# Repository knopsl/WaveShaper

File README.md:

# VC 4046 Wave Shaper

**Prototype has been tested, some issues found. Corrected version not yet tested! ASSUME NOTHING WORKS UNTIL THIS NOTICE IS REMOVED!**

This is a modification of the Barton Musical Circuits [4046 Wave Shaper](http://www.bartonmusicalcircuits.com/4046/), a module described by Barton as follows:

> This is an all analog synthesizer module used to create new timbres and waveforms with your existing VCOs. It uses a CD4046 phase locked loop chip in combination with a binary counter to multiply the frequency of the input signal. It then has 7 outputs divided down from that multiplied frequency which are mixed together. It's simple to use and has a distinct sound.

In Barton's design the seven signals (which are 0, 1, 2, and 3 octaves above and below the input signal) go into a simple mixer with a potentiometer attenuator on each channel to produce the module output. This modification replaces that simple mixer with a voltage controlled mixer, allowing use of control voltages to modulate the mix. If any of the seven control voltage jacks does not have anything plugged in, the CV is normalled to +10 V allowing the pot to behave like a signal attenuator.

An additional modification to Barton's design is that the gain on the output stage can be varied using a pot on the panel. This allows reducing the gain to avoid clipping when mixing multiple large signals, avoiding the need to turn down all the channel pots and allowing use of their full range.

The module consists of a front panel and three PCBs. One of these is the PCB for the original 4046 Wave Shaper, available from Barton, assembled mostly as designed but with a few things changed. The second is a PCB holding the board mounted pots and switch as well as the parts associated with the voltage controlled mixer and the power input section. The third just holds the board mounted input and output jacks.

## Photos

to be added

## Documentation

* [Schematic](Docs/waveshaper.pdf)
* PCB layout: [front](Docs/waveshaper_layout_front.pdf), [back](Docs/waveshaper_layout_back.pdf)
* [BOM](Docs/waveshaper_bom.md)
* [Build notes](Docs/build.md)

## GitHub repository

* [https://github.com/holmesrichards/WaveShaper](https://github.com/holmesrichards/WaveShaper)

## Submodules

This repo uses submodules aoKicad and Kosmo_panel, needed by KiCad. To clone:

```
git clone git@github.com:holmesrichards/WaveShaper.git
git submodule init
git submodule update
```

Alternatively do

```
git clone --recurse-submodules git@github.com:holmesrichards/WaveShaper.git
```

Or if you download the repository as a zip file, you must also click on the "aoKicad" and "Kosmo\_panel" links on the GitHub page (they'll have "@ something" after them) and download them as separate zip files which you can unzip into this repo's aoKicad and Kosmo\_panel directories.

If desired, copy the files from aoKicad and Kosmo\_panel to wherever you prefer (your KiCad user library directory, for instance, if you have one). Then in KiCad, add symbol libraries 

```
aoKicad/ao_symbols
Kosmo_panel/Kosmo
```
and footprint libraries 
```
aoKicad/ao_tht
Kosmo_panel/Kosmo_panel.
```

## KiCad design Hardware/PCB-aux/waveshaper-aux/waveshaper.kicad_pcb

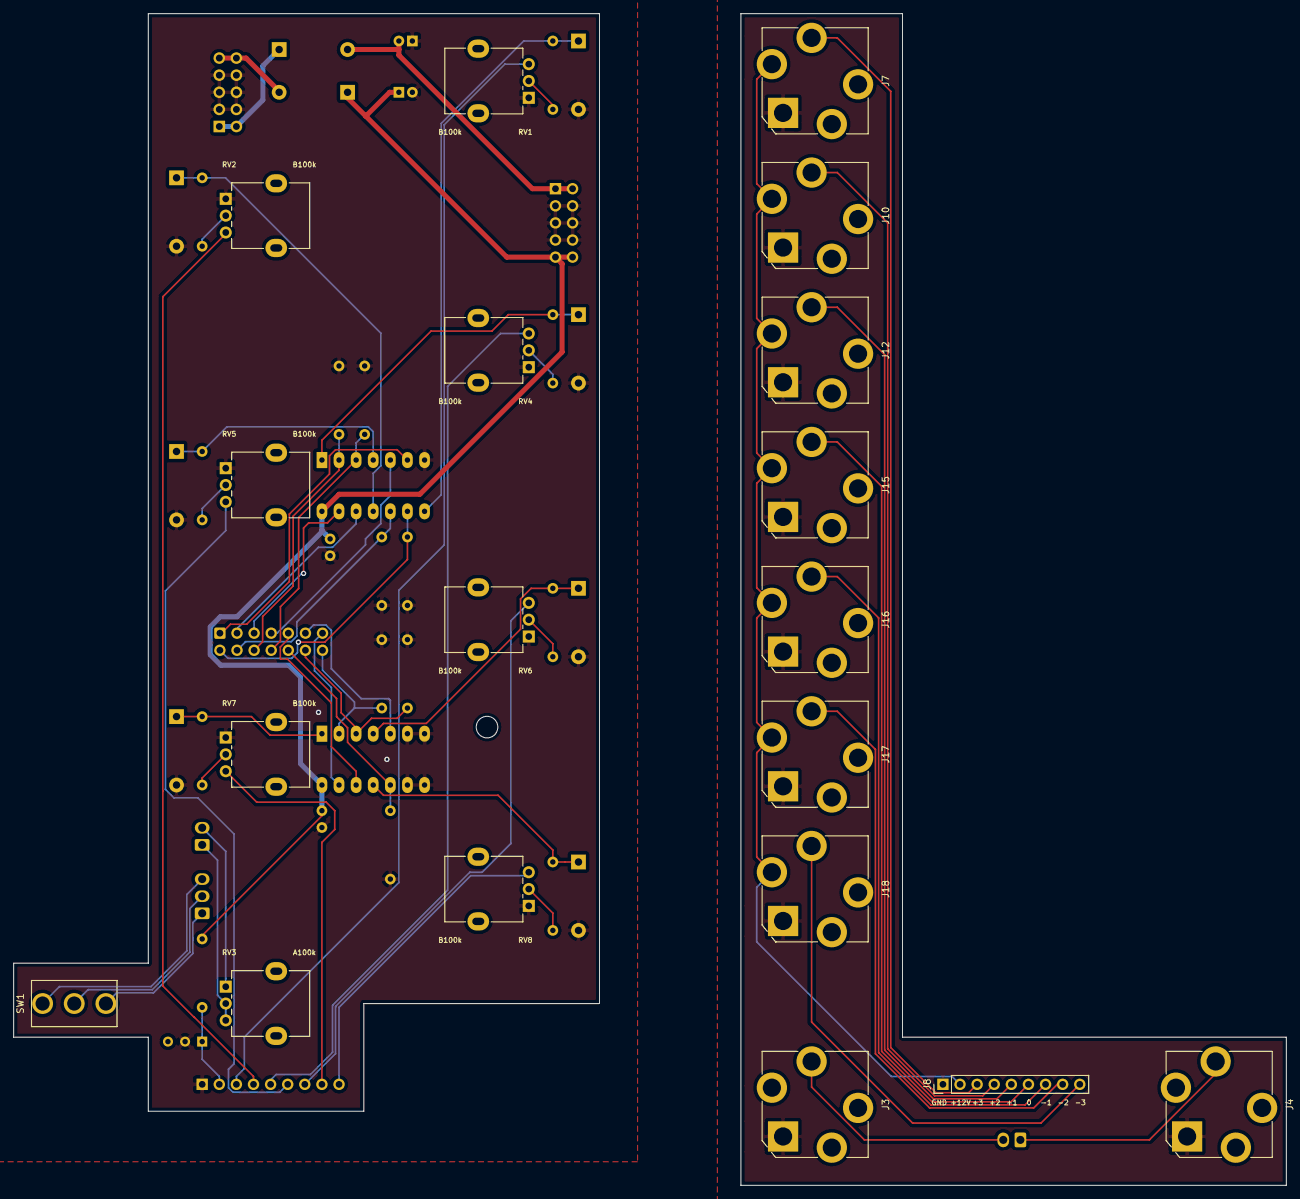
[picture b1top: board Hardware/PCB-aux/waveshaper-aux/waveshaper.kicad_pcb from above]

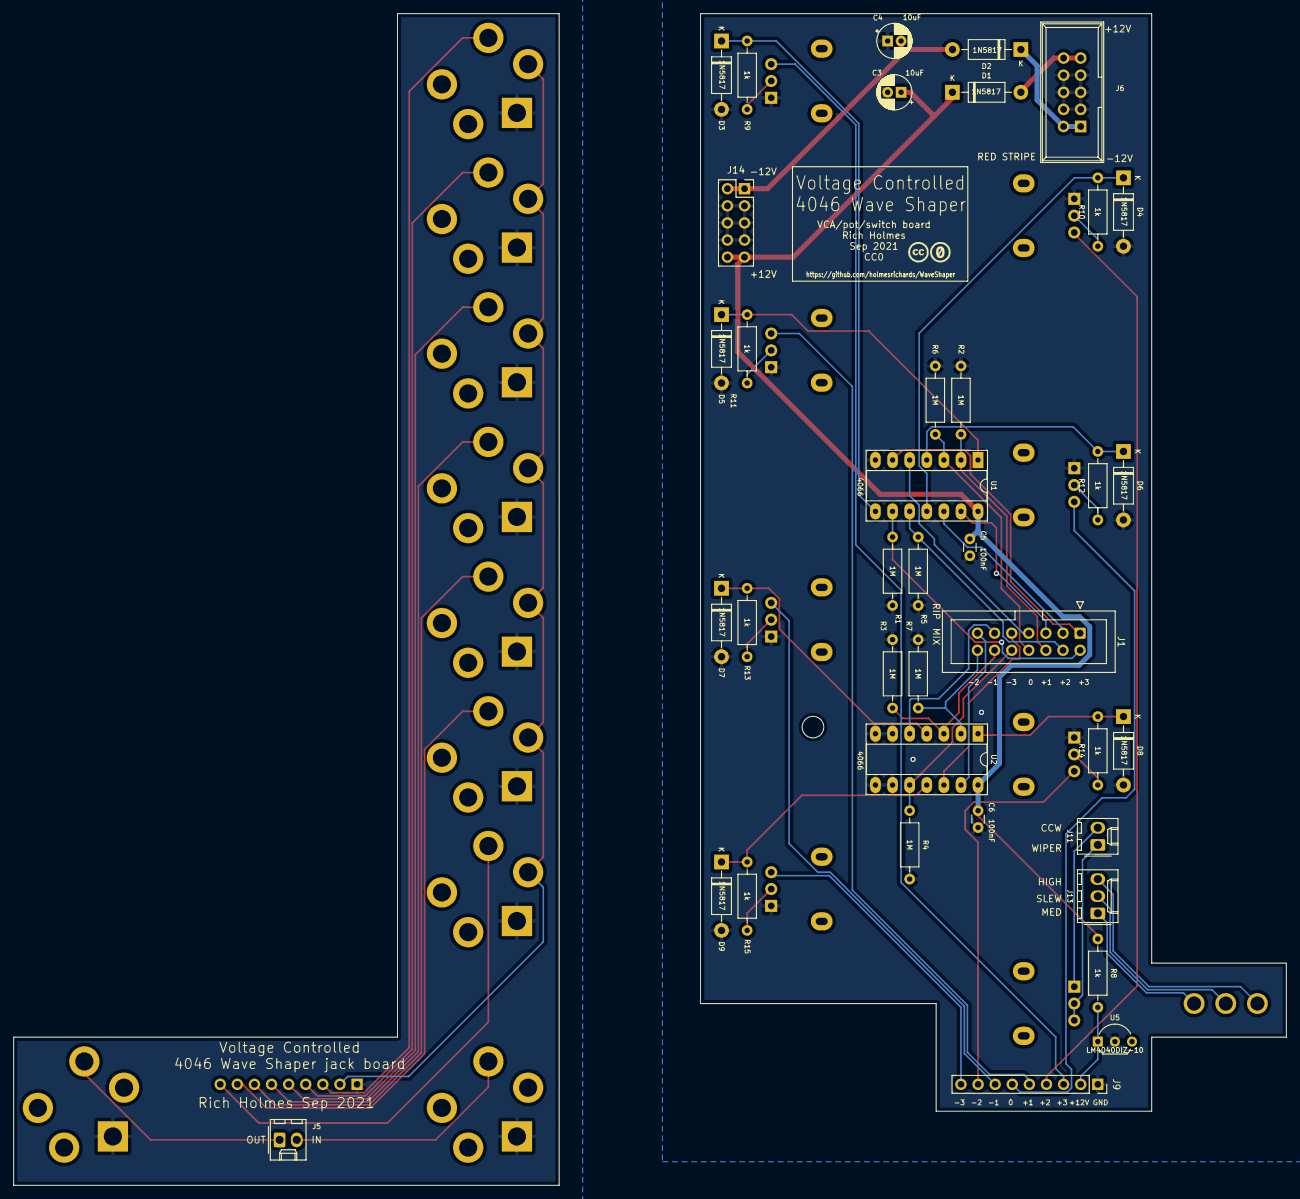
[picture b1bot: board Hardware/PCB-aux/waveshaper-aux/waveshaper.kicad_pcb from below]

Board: 2 copper layers, 87.0 x 163.0 mm, 60 parts (39 on the bottom side), 57 nets.

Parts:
C3, C4: 10uF; CP_Radial_D5.0mm_P2.00mm
C5, C6: 100nF; C_Disc_D3.0mm_W1.6mm_P2.50mm
D1, D2, D3, D4, D5, D6, D7, D8, D9: 1N5817; D_DO-41_SOD81_P10.16mm_Horizontal
GRAF1: CC0 logo; CC0_logo
GRAF2: Holes; waveshaper-holes
H1: MountingHole; MountingHole_3.2mm_M3
J1: 2x7 IDC header; IDC-Header_2x07_P2.54mm_Vertical
J3, J4: AudioJack2; Jack_6.35mm_PJ_629HAN
J5, J11: 2_pin_Molex_header; Molex_KK-254_AE-6410-02A_1x02_P2.54mm_Vertical
J6: EURO_PWR_2x5; Power_Header
J7, J10, J12, J15, J16, J17, J18: AudioJack2_SwitchT; Jack_6.35mm_PJ_629HAN
J8: Conn_01x9; PinHeader_1x09_P2.54mm_Vertical
J9: Conn_01x9; PinSocket_1x09_P2.54mm_Vertical
J13: 3_pin_Molex_header; Molex_KK-254_AE-6410-03A_1x03_P2.54mm_Vertical
J14: 2x5 pin socket; PinSocket_2x05_P2.54mm_Vertical
R1, R2, R3, R4, R5, R6, R7: 1M; R_Axial_DIN0207_L6.3mm_D2.5mm_P10.16mm_Horizontal
R8, R9, R10, R11, R12, R13, R14, R15: 1k; R_Axial_DIN0207_L6.3mm_D2.5mm_P10.16mm_Horizontal
RV1, RV2, RV4, RV5, RV6, RV7, RV8: B100k; Potentiometer_Alpha_RD901F-40-00D_Single_Vertical
RV3: A100k; Potentiometer_Alpha_RD901F-40-00D_Single_Vertical
SW1: SW_SPDT; SPDT-toggle-switch-1M-series
U1, U2: 4066; DIP-14_W7.62mm_Socket_LongPads
U5: LM4040DIZ-10; TO-92_Inline_Wide

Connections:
+10V: J9.2, R8.2, U5.1
+12V: C3.1, C5.1, C6.1, D1.1, J14.9, J14.10, R8.1, U1.14, U2.14
-12V: C4.2, D2.2, J14.1, J14.2
/Panel and power/+12V_IN: D1.2, J6.9, J6.10
/Panel and power/-12V_IN: D2.1, J6.1, J6.2
/Panel and power/CVIN_0: J8.6, J15.T
/Panel and power/CVIN_+1: J8.5, J12.T
/Panel and power/CVIN_+2: J8.4, J10.T
/Panel and power/CVIN_+3: J7.T, J8.3
/Panel and power/CVIN_-1: J8.7, J16.T
/Panel and power/CVIN_-2: J8.8, J17.T
/Panel and power/CVIN_-3: J8.9, J18.T
/Panel and power/IN: J3.T, J5.2
/Panel and power/LEVEL_CCW: J11.2, RV3.1
/Panel and power/LEVEL_WIPER: J11.1, RV3.2, RV3.3
/Panel and power/OUT: J4.T, J5.1
/Panel and power/SLEW: J13.2, SW1.2
/Panel and power/SL_HIGH: J13.3, SW1.3
/Panel and power/SL_MED: J13.1, SW1.1
/RIPOUT_0: J1.7, U1.5
/RIPOUT_+1: J1.5, U1.13
/RIPOUT_+2: J1.3, U1.12
/RIPOUT_+3: J1.1, U1.6
/RIPOUT_-1: J1.11, U2.5
/RIPOUT_-2: J1.13, U2.13
/RIPOUT_-3: J1.9, U2.12
CV_0: D6.1, R12.2, U1.4
CV_+1: D5.1, R11.2, U1.1
CV_+2: D4.1, R10.2, U1.11
CV_+3: D3.1, R9.2, U1.8
CV_-1: D7.1, R13.2, U2.4
CV_-2: D8.1, R14.2, U2.1
CV_-3: D9.1, R15.2, U2.11
GND: C3.2, C4.1, C5.2, C6.2, D3.2, D4.2, D5.2, D6.2, D7.2, D8.2, D9.2, J6.3, J6.4, J6.5, J6.6, J6.7, J6.8, J9.1, J14.3, J14.4, J14.5, J14.6, J14.7, J14.8, R1.2, R2.2, R3.2, R4.2, R5.2, R6.2, R7.2, RV1.1, RV2.1, RV4.1, RV5.1, RV6.1, RV7.1, RV8.1, U1.7, U2.6, U2.7, U2.8, U2.9, U5.2
GND1: J3.S, J4.S, J7.S, J8.1, J10.S, J12.S, J15.S, J16.S, J17.S, J18.S
J10V: J7.TN, J8.2, J10.TN, J12.TN, J15.TN, J16.TN, J17.TN, J18.TN
MIXIN_0: J1.8, R6.1, U1.3
MIXIN_+1: J1.6, R2.1, U1.2
MIXIN_+2: J1.4, R5.1, U1.10
MIXIN_+3: J1.2, R1.1, U1.9
MIXIN_-1: J1.12, R3.1, U2.3
MIXIN_-2: J1.14, R7.1, U2.2
MIXIN_-3: J1.10, R4.1, U2.10
unnamed: J9.3, RV1.3
unnamed: J9.4, RV2.3
unnamed: J9.5, RV4.3
unnamed: J9.6, RV5.3
unnamed: J9.7, RV6.3
unnamed: J9.8, RV7.3
unnamed: J9.9, RV8.3
unnamed: R9.1, RV1.2
unnamed: R10.1, RV2.2
unnamed: R11.1, RV4.2
unnamed: R12.1, RV5.2
unnamed: R13.1, RV6.2
unnamed: R14.1, RV7.2
unnamed: R15.1, RV8.2

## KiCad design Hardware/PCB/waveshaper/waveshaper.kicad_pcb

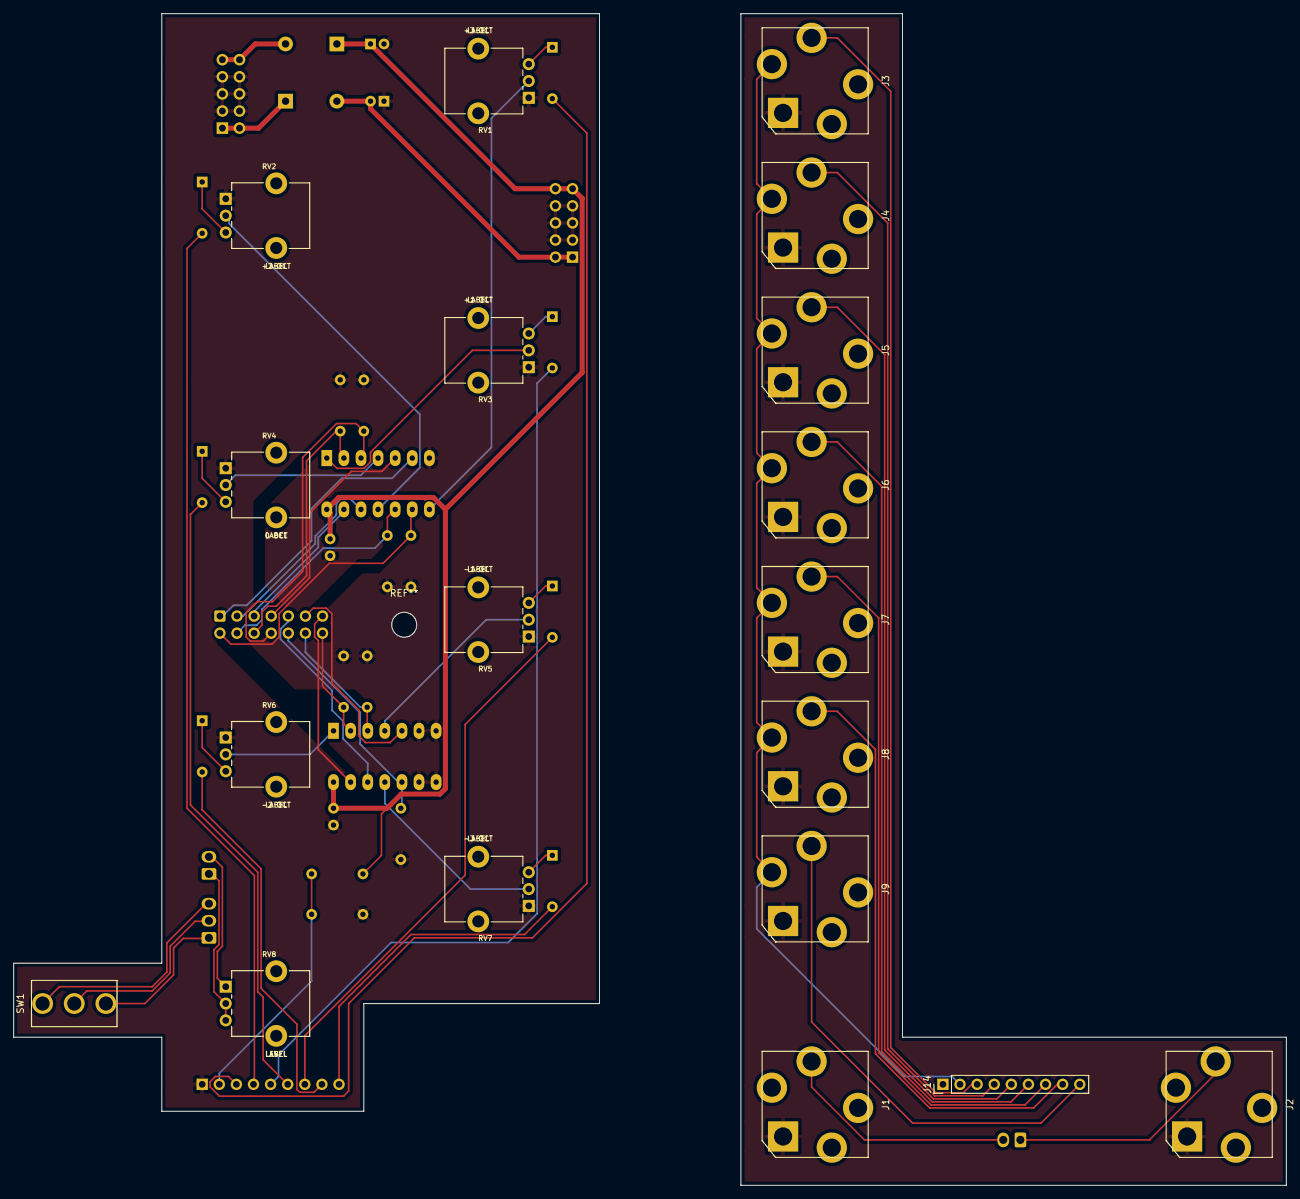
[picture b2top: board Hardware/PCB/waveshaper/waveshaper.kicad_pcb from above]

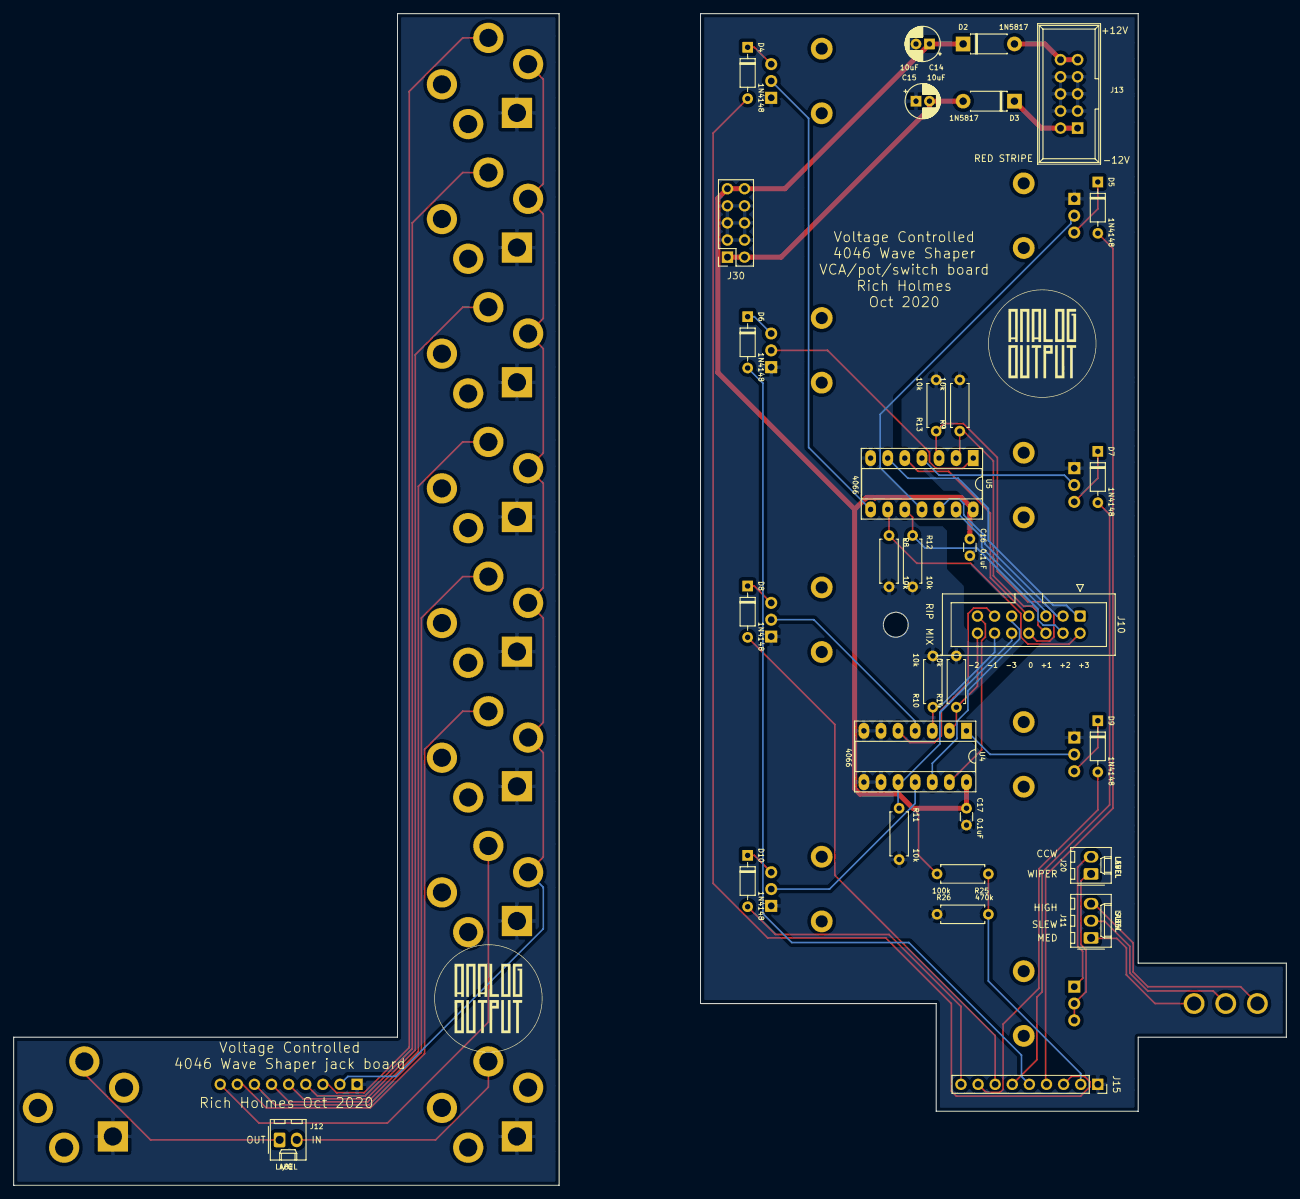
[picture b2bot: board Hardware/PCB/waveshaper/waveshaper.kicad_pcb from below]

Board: 2 copper layers, 189.0 x 174.0 mm, 50 parts (31 on the bottom side), 56 nets.

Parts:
C14, C15: 10uF; CP_Radial_D5.0mm_P2.00mm
C16, C17: 0.1uF; C_Disc_D3.0mm_W1.6mm_P2.50mm
D2, D3: 1N5817; D_DO-41_SOD81_P7.62mm_Horizontal
D4, D5, D6, D7, D8, D9, D10: 1N4148; D_DO-35_SOD27_P7.62mm_Horizontal
J1, J2, J3, J4, J5, J6, J7, J8, J9: AudioJack2_SwitchT; Jack_6.35mm_PJ_629HAN
J10: 2x7 IDC header; IDC-Header_2x07_P2.54mm_Vertical
J11: Conn_01x03; Molex_KK-254_AE-6410-03A_1x03_P2.54mm_Vertical
J12, J20: Conn_01x02; Molex_KK-254_AE-6410-02A_1x02_P2.54mm_Vertical
J13: EURO_PWR_2x5; Power_Header
J14: Conn_01x9; PinHeader_1x09_P2.54mm_Vertical
J15: Conn_01x9; PinSocket_1x09_P2.54mm_Vertical
J30: 2x5 pin socket; PinSocket_2x05_P2.54mm_Vertical
R8, R9, R10, R11, R12, R13, R14: 10k; R_Axial_DIN0207_L6.3mm_D2.5mm_P7.62mm_Horizontal
R25: 100k; R_Axial_DIN0207_L6.3mm_D2.5mm_P7.62mm_Horizontal
R26: 470k; R_Axial_DIN0207_L6.3mm_D2.5mm_P7.62mm_Horizontal
RV1, RV2, RV3, RV4, RV5, RV6, RV7: B100k; Potentiometer_Alpha_RD901F-40-00D_Single_Vertical_CircularH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
RV8: A100k; Potentiometer_Alpha_RD901F-40-00D_Single_Vertical_CircularH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
SW1: SW_SPDT; SPDT-toggle-switch-1M-series
U4, U5: 4066; DIP-14_W7.62mm_Socket_LongPads

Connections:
+10V: J15.2, R25.1, R26.2
+12V: C14.1, C16.1, C17.1, D2.1, J30.9, J30.10, R25.2, U4.14, U5.14
-12V: C15.2, D3.2, J30.1, J30.2
/Panel and power/CVIN_0: J6.T, J14.6
/Panel and power/CVIN_+1: J5.T, J14.5
/Panel and power/CVIN_+2: J4.T, J14.4
/Panel and power/CVIN_+3: J3.T, J14.3
/Panel and power/CVIN_-1: J7.T, J14.7
/Panel and power/CVIN_-2: J8.T, J14.8
/Panel and power/CVIN_-3: J9.T, J14.9
/Panel and power/IN: J1.T, J12.2
/Panel and power/LEVEL_CCW: J20.2, RV8.1
/Panel and power/LEVEL_WIPER: J20.1, RV8.2, RV8.3
/Panel and power/OUT: J2.T, J12.1
/Panel and power/SLEW: J11.2, SW1.2
/Panel and power/SL_HIGH: J11.3, SW1.3
/Panel and power/SL_MED: J11.1, SW1.1
/RIPOUT_0: J10.7, U5.5
/RIPOUT_+1: J10.5, U5.13
/RIPOUT_+2: J10.3, U5.12
/RIPOUT_+3: J10.1, U5.6
/RIPOUT_-1: J10.11, U4.5
/RIPOUT_-2: J10.13, U4.13
/RIPOUT_-3: J10.9, U4.12
CV_0: RV4.2, U5.4
CV_+1: RV3.2, U5.1
CV_+2: RV2.2, U5.11
CV_+3: RV1.2, U5.8
CV_-1: RV5.2, U4.4
CV_-2: RV6.2, U4.1
CV_-3: RV7.2, U4.11
GND: C14.2, C15.1, C16.2, C17.2, J1.S, J2.S, J3.S, J4.S, J5.S, J6.S, J7.S, J8.S, J9.S, J13.3, J13.4, J13.5, J13.6, J13.7, J13.8, J14.1, J15.1, J30.3, J30.4, J30.5, J30.6, J30.7, J30.8, R8.2, R9.2, R10.2, R11.2, R12.2, R13.2, R14.2, R26.1, RV1.1, RV2.1, RV3.1, RV4.1, RV5.1, RV6.1, RV7.1, U4.6, U4.7, U4.8, U4.9, U5.7
MIXIN_0: J10.8, R13.1, U5.3
MIXIN_+1: J10.6, R9.1, U5.2
MIXIN_+2: J10.4, R12.1, U5.10
MIXIN_+3: J10.2, R8.1, U5.9
MIXIN_-1: J10.12, R10.1, U4.3
MIXIN_-2: J10.14, R14.1, U4.2
MIXIN_-3: J10.10, R11.1, U4.10
unnamed: D2.2, J13.9, J13.10
unnamed: D3.1, J13.1, J13.2
unnamed: D4.1, RV1.3
unnamed: D4.2, J15.3
unnamed: D5.1, RV2.3
unnamed: D5.2, J15.4
unnamed: D6.1, RV3.3
unnamed: D6.2, J15.5
unnamed: D7.1, RV4.3
unnamed: D7.2, J15.6
unnamed: D8.1, RV5.3
unnamed: D8.2, J15.7
unnamed: D9.1, RV6.3
unnamed: D9.2, J15.8
unnamed: D10.1, RV7.3
unnamed: D10.2, J15.9
unnamed: J3.TN, J4.TN, J5.TN, J6.TN, J7.TN, J8.TN, J9.TN, J14.2

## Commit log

2020-09-27 Default README
2020-09-27 rm unused .sch
2020-10-03 Overdue commit: Boards redesign, docs folder
2020-10-09 Various tweaks
2020-10-25 14 pin connector -> IDC
2020-11-21 Directory reorg, panel work
2021-01-02 Footprints updated
2021-01-17 Include lib table files; new Gerbers
2021-02-19 Footprint update
2021-02-28 Update .gitignore, DIN5
2021-04-30 PCB tweak, font correction on panel
2021-08-07 Final tweaks before fabbing; Kosmo_panel lib update
2021-08-12 submodules
2021-08-12 submodules uh
2021-08-12 submodules uh uh
2021-08-12 submodules ah
2021-08-12 submodules info in README
2021-08-12 Gerbers
2021-08-12 submodule update
2021-08-12 Update submodule
2021-08-20 No NPTH specialization
2021-08-21 relocate libraries
2021-08-21 rm project libraries
2021-08-27 submodule doc
2021-08-29 Documentation, some cosmetic sch/PCB changes
2021-09-10 Mounting hole; parallel Schottkys instead of series switchers
2021-09-11 Fix power polarity
2021-09-12 Docs and minor corrections
2021-09-12 Add warning
2021-09-12 rm bad Gerbers
2021-09-12 Big redo: Add voltage ref, buffers; rm diodes
2021-09-13 Yes we need Schottkys
2021-09-13 Make pulldowns 100k
2021-09-13 Use TL074
2021-09-13 Revert "Use TL074"
    This reverts commit 1a999078385277cd582d072a8d94e8801a268032.
2021-09-15 rm op amp, reroute
2021-09-19 Trace tweaks, Gerbers
2021-09-22 Change pot footprint, new Gerbers
2021-09-22 Tiny adjustment
2021-09-23 Pre fab tweaks, new Gerbers, clarify schematic for jacks connections
